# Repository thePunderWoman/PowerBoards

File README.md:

# Power Boards

Small PCBs for power regulation and distribution.

Each board's electrical design is written in [Stackup](https://github.com/stackup-eda/stackup) KDL, which
is the source of truth for the circuit; there are no KiCad schematics. The layout is done in KiCad
(currently 10), linked to the KDL through a `.stackup_sch` file and synced with the Stackup KiCad plugin.

## Boards

| Board | Folder | Purpose | Status |
|---|---|---|---|
| Regulator | [`PCB/regulator/`](PCB/regulator) | Power regulation | Not started |
| Distribution | [`PCB/distribution/`](PCB/distribution) | Six interchangeable power terminals (any one can be the input) over shared V+ and GND planes, WAGO 2601 lever terminals | Initial layout done |

## Repository layout

| Path | Contents |
|---|---|
| [`manifest.kdl`](manifest.kdl) | Stackup version and the parts library, pinned by commit. Shared by every board |
| `PCB/<board>/` | One folder per board: its KiCad project (`<board>.kicad_pro`, `.kicad_pcb`, `.stackup_sch`) and the folders below |
| `PCB/<board>/stackup/` | `board.kdl` (circuit), `parts.kdl` (board-specific parts), `purchasing.kdl` (manufacturer and supplier choices) |
| `PCB/<board>/diagrams/` | Layout floorplans for circuits with real layout stakes (switching loops, thermal pads, high-current paths) |
| `PCB/<board>/analysis/` | Generated analysis output. Only `manifest.json` is committed |
| `PCB/<board>/production/` | Fab outputs: `bom/`, `gerbers/`, `jlcpcb/`, `placement/` |
| [`PCB/libraries/`](PCB/libraries) | KiCad symbols, footprints and 3D models shared by all boards |
| [`PCB/datasheets/`](PCB/datasheets) | Manufacturer datasheets for the parts used, shared by all boards |
| [`scripts/spice/`](scripts/spice) | ngspice simulations of the power, enable and protection circuits |
| [`graphics/`](graphics) | Logos and images |

To add a board, create `PCB/<board>/` with the same subfolders as an existing one and add it to the
table above.

## Working on a board

Run these from the repository root.

```bash
# Check the circuit
stackup check PCB/<board>/stackup/board.kdl

# Export the purchasing BOM
stackup bom PCB/<board>/stackup/board.kdl --locked -o <board>-bom.csv
```

After `stackup check` passes, open `PCB/<board>/<board>.kicad_pcb` in KiCad and sync it with the Stackup
plugin.

## Contributing

All changes go through pull requests; nothing is pushed directly to `main`. History is kept linear, so
PRs land by rebase.

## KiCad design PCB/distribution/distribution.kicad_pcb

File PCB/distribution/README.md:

# Distribution Board

Six identical 2-pole terminals share a V+ plane (`VPWR`, top copper) and a ground plane (`GND`,
bottom copper). Any terminal can be the input; the other five are outputs. There are no active or
passive components.

The electrical design is in [Stackup KDL](stackup/board.kdl). The KiCad PCB
(`distribution.kicad_pcb`) is linked to it through `distribution.stackup_sch`; sync it with the Stackup
KiCad plugin. Run `stackup check PCB/distribution/stackup/board.kdl` from the repository root
before syncing.

## Hardware overview

| Ref | Function | Part |
|---|---|---|
| J1-J6 | Power terminal, input or output | WAGO 2601-1102 |

Every terminal has pin 1 (square pad, `+` on the silkscreen) on `VPWR` and pin 2 (`-`) on `GND`.

## Terminal: WAGO 2601-1102

Lever-actuated Push-in CAGE CLAMP, 2-pole, 3.5 mm pitch, wire entry parallel to the PCB.
From the [WAGO data sheet](../datasheets/WAGO_2601-1102.pdf) (version 25.01.2023):

| Spec | Value | Source |
|---|---|---|
| Wire, solid | 0.14-1.5 mm² / 26-16 AWG | p. 2 |
| Wire, fine-stranded | 0.2-1.5 mm² / 24-16 AWG | p. 2 |
| Strip length | 8-9 mm | p. 2 |
| Rated current | 17.5 A (IEC/EN 60664-1); 10 A (UL 1059 / CSA, Use Groups B and D) | p. 2 |
| Wire entry angle to PCB | 0° | p. 2 |
| Solder pins | 2 per pole, rows 5 mm apart, 1.2 (+0.1) mm hole | p. 1, p. 3 |

The 2601-3102 is the vertical, top-entry version of the same block; it is not a substitute.

## Design decisions

- **Current limit is the input terminal.** Whichever terminal is used as the input carries the sum of
  all the outputs. The design limit is 10 A total, the terminal's UL rating, with 16 AWG wire.
- **No input or output labels.** Any terminal can be the input, so the silkscreen marks only `+` and `-`.
- **3 x 2 grid, rows back to back.** J1-J3 form the top row, rotated 180° so their wires enter from
  the top edge. J4-J6 form the bottom row, with wires entering from the
  bottom edge. Columns are on a 10 mm pitch (8.5 mm body plus room to work the levers), and an 8 mm gap
  between the rows holds the polarity labels. Seen from its own edge, every terminal has `+` on the left.
- **Wire entry faces are flush with the top and bottom board edges**, so the wires leave the board and
  the levers (16.58 mm deep including the lever, versus a 14.5 mm body) overhang the edge. This puts the
  footprints' silkscreen outlines across the edge: the 12 `silk_edge_clearance` DRC warnings are
  expected and the fab clips that silkscreen.
- **Four M3 mounting holes, one per corner.** KiCad `MountingHole_3.2mm_M3` (3.2 mm unplated), placed
  on side extensions beside the terminals, with each hole centre 4.5 mm from the nearest terminal body.
  They are board-only footprints in the layout, not Stackup parts: Stackup sync leaves board-only
  footprints alone, and they stay out of the BOM and placement files.
- **Copper keep-out around each hole.** An 8 mm diameter rule area on both copper layers keeps the V+ and
  GND planes away from the screw head and standoff. Otherwise a metal screw would sit on V+ copper on
  top and GND on the bottom with only solder mask between them.
- **Planes, not traces.** At 10 A, IPC-2221 needs about 7.2 mm of 1 oz outer copper for a 10 °C rise.
  Each plane spans the whole 45.5 x 37 mm board. Pads join their plane through thermal reliefs with
  1.0 mm spokes; with two solder pins per pole, that is 8 spokes (8 mm of copper) per pole.

## Bench checklist

- Before connecting a load, check continuity between all six `+` pins and between all six `-` pins, and
  confirm there is no short between V+ and GND.
- Run the full intended load through the input and one output, and check the input terminal and the
  board near it for heating.

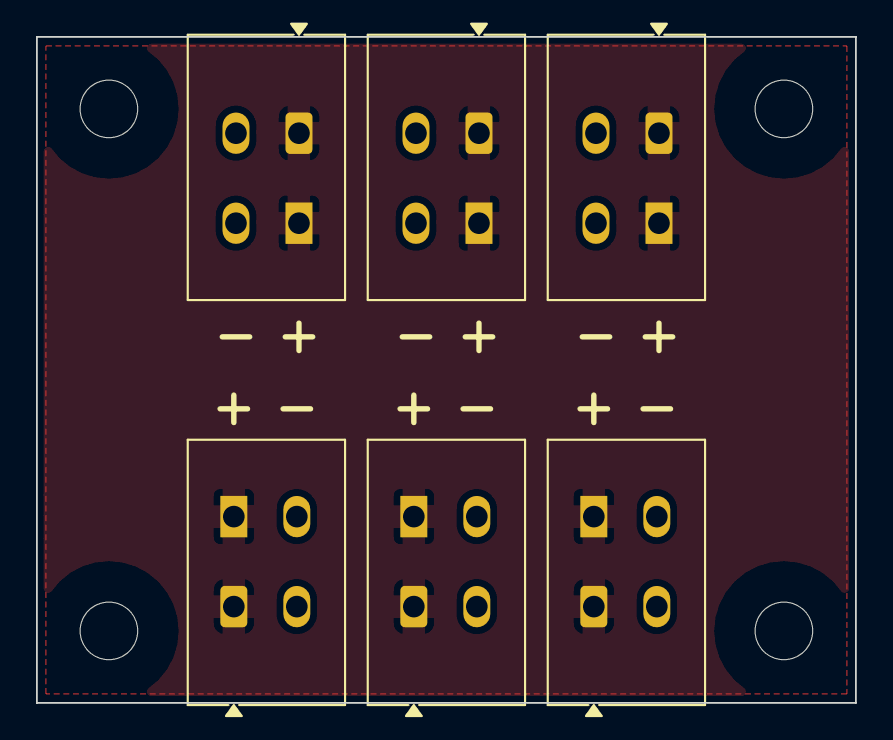
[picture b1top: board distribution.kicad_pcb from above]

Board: 2 copper layers, 45.5 x 37.0 mm, 10 parts (0 on the bottom side), 2 nets, no tracks yet.

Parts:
H1, H2, H3, H4: MountingHole_3.2mm_M3
J1, J2, J3, J4, J5, J6: WAGO 2601-1102; WAGO_2601-1102_Horizontal

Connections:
GND: J1.2, J2.2, J3.2, J4.2, J5.2, J6.2
VPWR: J1.1, J2.1, J3.1, J4.1, J5.1, J6.1
